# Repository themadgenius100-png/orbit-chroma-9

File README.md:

# Orbit-Chroma-9
A high-spec 9-key mechanical macro pad powered by a Seeeduino XIAO, featuring custom RGB LED lighting, an I2C OLED screen for live animations (like Bongo Cat!), and a rotary encoder knob for smooth desktop control.

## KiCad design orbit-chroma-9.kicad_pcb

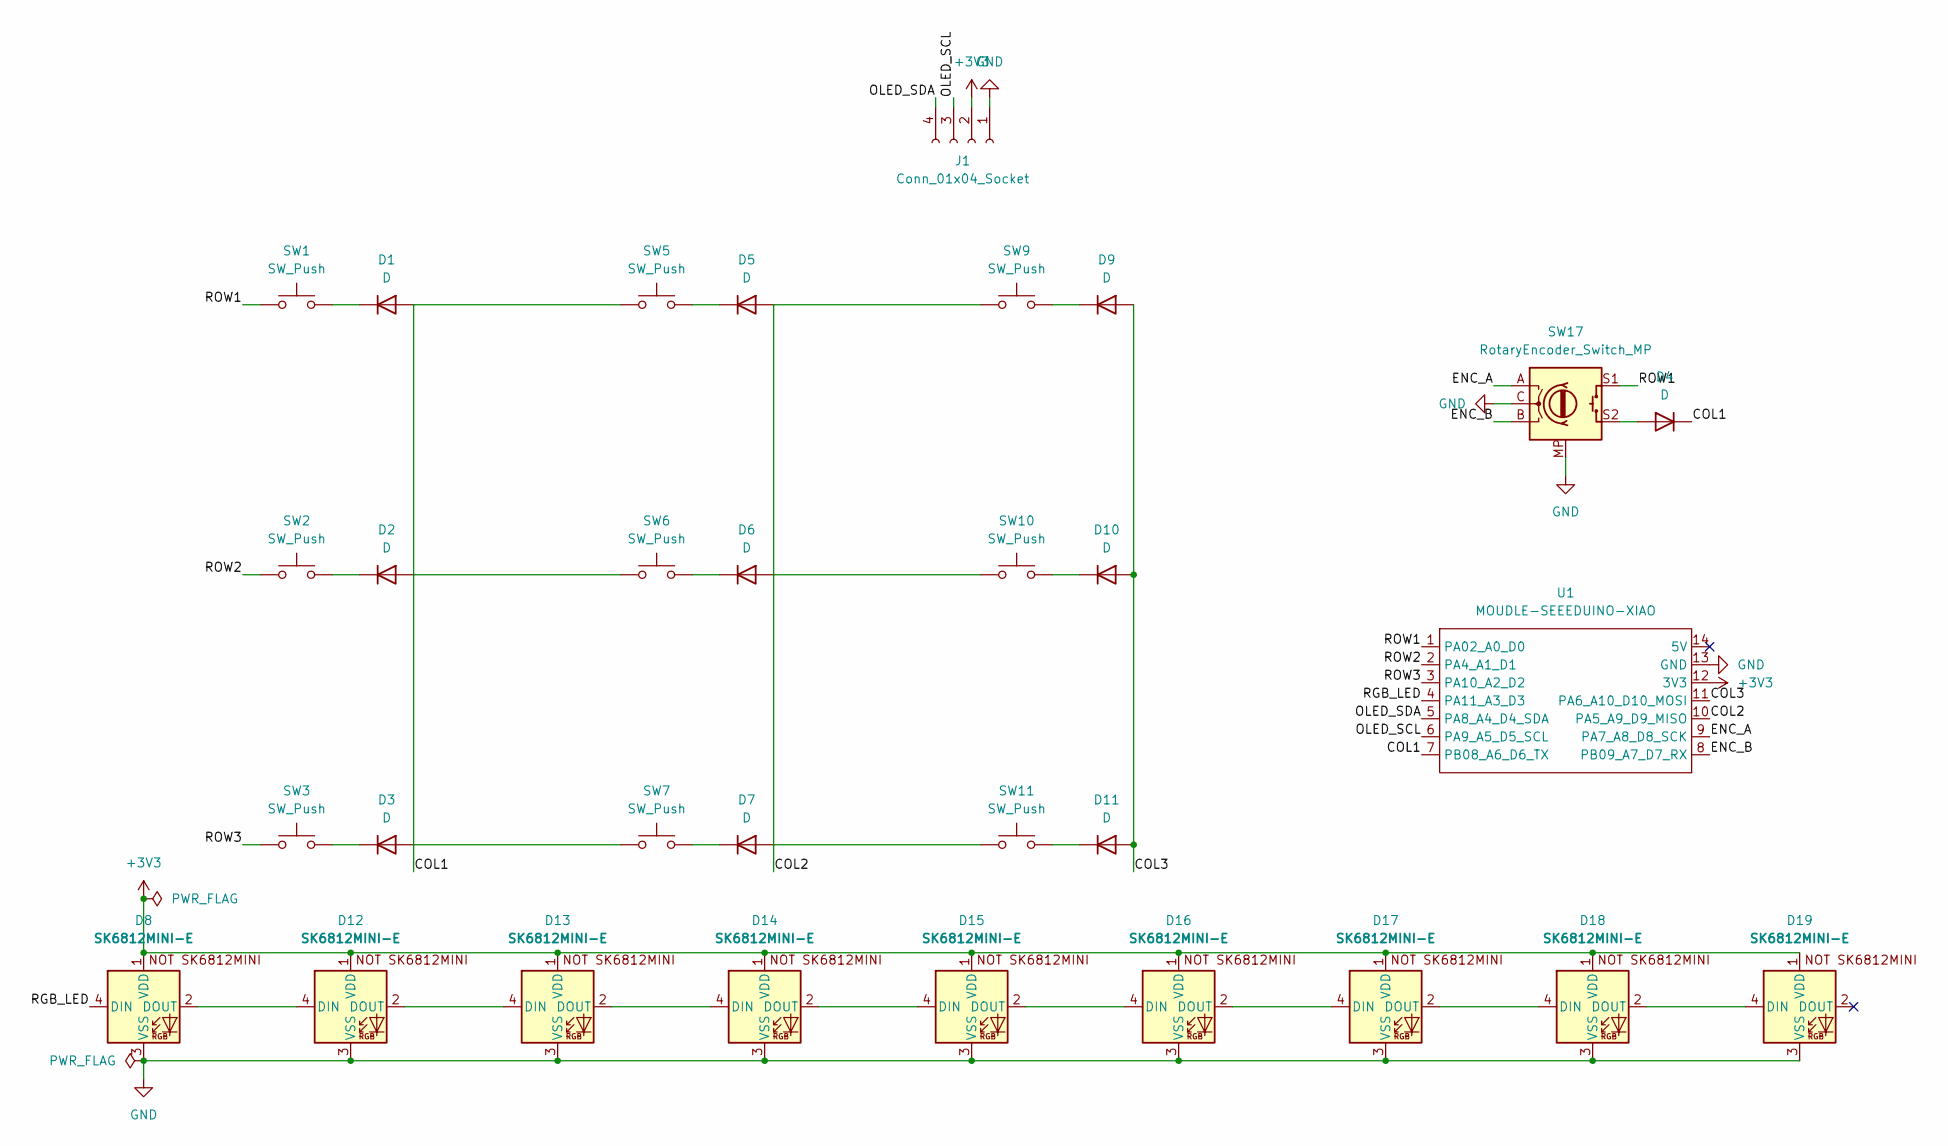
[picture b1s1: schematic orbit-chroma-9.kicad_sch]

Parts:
D1, D2, D3, D4, D5, D6, D7, D9, D10, D11: D; D_DO-35_SOD27_P7.62mm_Horizontal
D8, D12, D13, D14, D15, D16, D17, D18, D19: SK6812MINI-E; LED_SK6812MINI-E_3.2x2.8mm_P1.5mm_ReverseMount
J1: Conn_01x04_Socket; PinHeader_1x04_P2.54mm_Vertical
SW1, SW2, SW3, SW5, SW6, SW7, SW9, SW10, SW11: SW_Push; SW_Cherry_MX_1.00u_PCB
SW17: RotaryEncoder_Switch_MP; RotaryEncoder_Alps_EC11E-Switch_Vertical_H20mm
U1: MOUDLE-SEEEDUINO-XIAO; DIP-14_W7.62mm

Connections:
+3V3: D8.1 (VDD), D12.1 (VDD), D13.1 (VDD), D14.1 (VDD), D15.1 (VDD), D16.1 (VDD), D17.1 (VDD), D18.1 (VDD), D19.1 (VDD), J1.2, U1.12 (3V3)
/COL1: D1.2 (A), D4.1 (K), SW5.1, U1.7 (PB08_A6_D6_TX)
/COL2: D5.2 (A), SW9.1, U1.10 (PA5_A9_D9_MISO)
/COL3: D9.2 (A), D10.2 (A), D11.2 (A), U1.11 (PA6_A10_D10_MOSI)
/ENC_A: SW17.A, U1.9 (PA7_A8_D8_SCK)
/ENC_B: SW17.B, U1.8 (PB09_A7_D7_RX)
/OLED_SCL: J1.3, U1.6 (PA9_A5_D5_SCL)
/OLED_SDA: J1.4, U1.5 (PA8_A4_D4_SDA)
/RGB_LED: D8.4 (DIN), U1.4 (PA11_A3_D3)
/ROW1: SW1.1, SW17.S1, U1.1 (PA02_A0_D0)
/ROW2: SW2.1, U1.2 (PA4_A1_D1)
/ROW3: SW3.1, U1.3 (PA10_A2_D2)
GND: D8.3 (VSS), D12.3 (VSS), D13.3 (VSS), D14.3 (VSS), D15.3 (VSS), D16.3 (VSS), D17.3 (VSS), D18.3 (VSS), D19.3 (VSS), J1.1, SW17.C, SW17.MP, U1.13 (GND)
unnamed: D1.1 (K), SW1.2
unnamed: D2.2 (A), SW6.1
unnamed: D2.1 (K), SW2.2
unnamed: D3.2 (A), SW7.1
unnamed: D3.1 (K), SW3.2
unnamed: D4.2 (A), SW17.S2
unnamed: D5.1 (K), SW5.2
unnamed: D6.2 (A), SW10.1
unnamed: D6.1 (K), SW6.2
unnamed: D7.2 (A), SW11.1
unnamed: D7.1 (K), SW7.2
unnamed: D9.1 (K), SW9.2
unnamed: D10.1 (K), SW10.2
unnamed: D11.1 (K), SW11.2
unnamed: D8.2 (DOUT), D12.4 (DIN)
unnamed: D12.2 (DOUT), D13.4 (DIN)
unnamed: D13.2 (DOUT), D14.4 (DIN)
unnamed: D14.2 (DOUT), D15.4 (DIN)
unnamed: D15.2 (DOUT), D16.4 (DIN)
unnamed: D16.2 (DOUT), D17.4 (DIN)
unnamed: D17.2 (DOUT), D18.4 (DIN)
unnamed: D18.2 (DOUT), D19.4 (DIN)

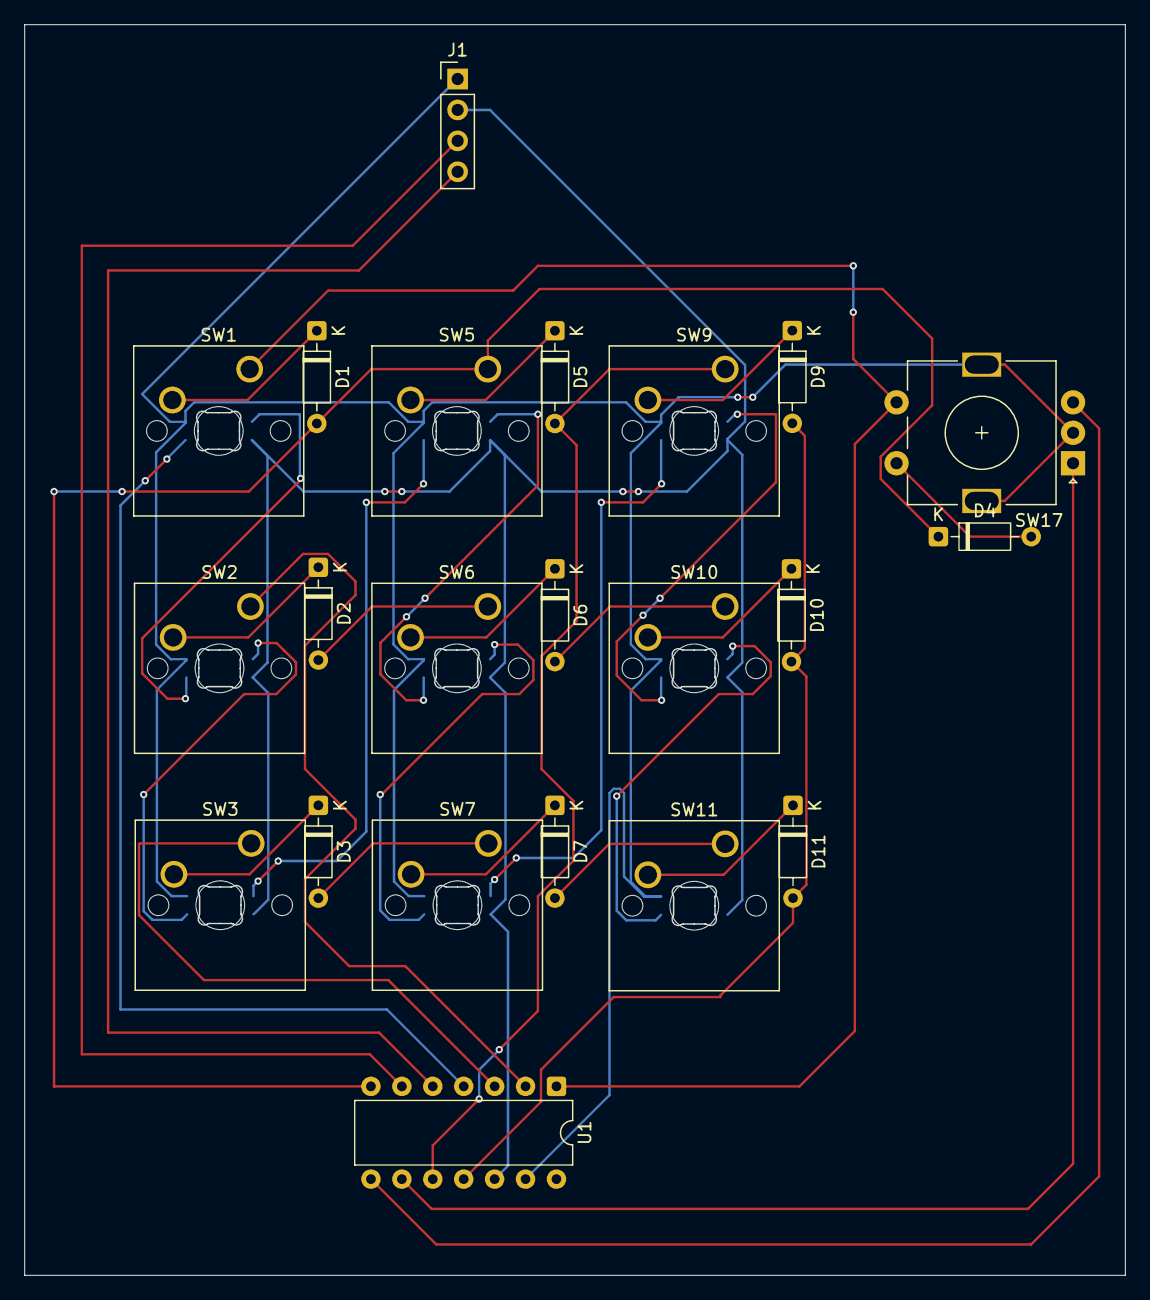
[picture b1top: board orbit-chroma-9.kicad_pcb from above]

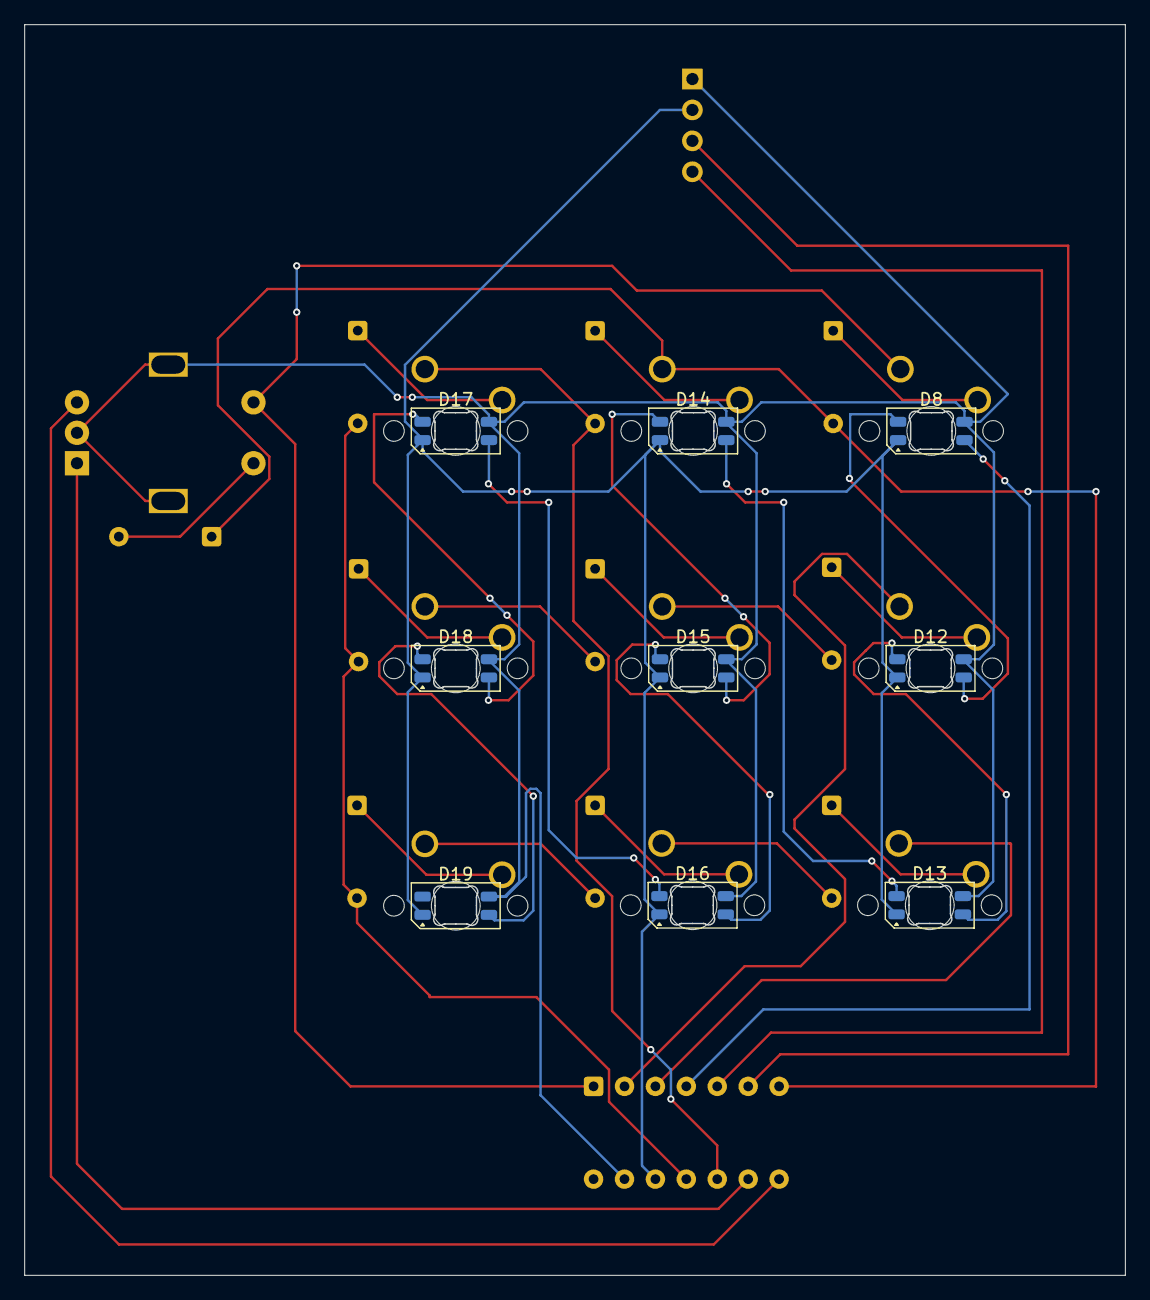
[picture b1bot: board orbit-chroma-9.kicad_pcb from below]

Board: 2 copper layers, 90.4 x 102.7 mm, 31 parts (9 on the bottom side), 35 nets.

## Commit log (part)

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2026-06-23 Rename project to Orbit-Chroma-9
2026-06-23 Add README file
2026-06-23 Rename README.md.txt to README.md
